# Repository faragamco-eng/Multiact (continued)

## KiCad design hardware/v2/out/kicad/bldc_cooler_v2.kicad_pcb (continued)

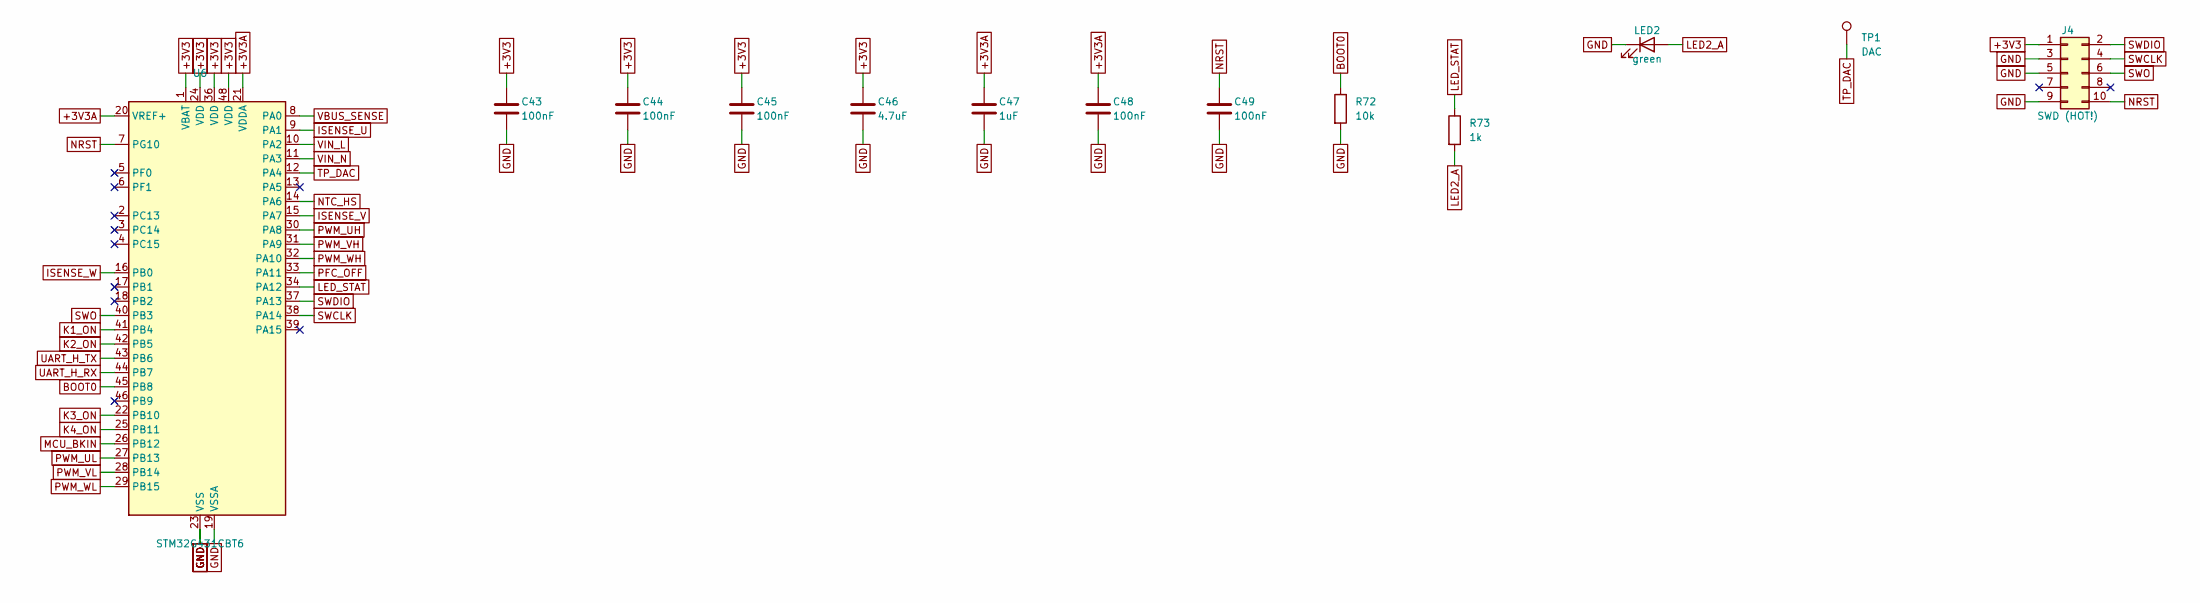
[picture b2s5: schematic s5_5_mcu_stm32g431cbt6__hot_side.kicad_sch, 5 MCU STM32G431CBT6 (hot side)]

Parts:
C43, C44, C45, C48, C49: 100nF; C_0603_1608Metric
C46: 4.7uF; C_0805_2012Metric
C47: 1uF; C_0603_1608Metric
J4: SWD (HOT!); PinHeader_2x05_P1.27mm_Vertical
LED2: green; LED_0805_2012Metric
R72: 10k; R_0603_1608Metric
R73: 1k; R_0603_1608Metric
TP1: DAC; TestPoint_Pad_D1.5mm
U6: STM32G431CBT6; LQFP-48_7x7mm_P0.5mm; MPN ST STM32G431CBT6

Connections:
+3V3: C43.1, C44.1, C45.1, C46.1, J4.1, U6.1 (VBAT), U6.24 (VDD), U6.36 (VDD), U6.48 (VDD); also elsewhere on the board
+3V3A: C47.1, C48.1, U6.20 (VREF+), U6.21 (VDDA); also elsewhere on the board
BOOT0: R72.1, U6.45 (PB8)
GND: C43.2, C44.2, C45.2, C46.2, C47.2, C48.2, C49.2, J4.3, J4.5, J4.9, LED2.1 (K), R72.2, U6.19 (VSSA), U6.23 (VSS), U6.35 (VSS), U6.47 (VSS); also elsewhere on the board
ISENSE_U: U6.9 (PA1); also elsewhere on the board
ISENSE_V: U6.15 (PA7); also elsewhere on the board
ISENSE_W: U6.16 (PB0); also elsewhere on the board
K1_ON: U6.41 (PB4); also elsewhere on the board
K2_ON: U6.42 (PB5); also elsewhere on the board
K3_ON: U6.22 (PB10); also elsewhere on the board
K4_ON: U6.25 (PB11); also elsewhere on the board
LED2_A: LED2.2 (A), R73.2
LED_STAT: R73.1, U6.34 (PA12)
MCU_BKIN: U6.26 (PB12); also elsewhere on the board
NRST: C49.1, J4.10, U6.7 (PG10)
NTC_HS: U6.14 (PA6); also elsewhere on the board
PFC_OFF: U6.33 (PA11); also elsewhere on the board
PWM_UH: U6.30 (PA8); also elsewhere on the board
PWM_UL: U6.27 (PB13); also elsewhere on the board
PWM_VH: U6.31 (PA9); also elsewhere on the board
PWM_VL: U6.28 (PB14); also elsewhere on the board
PWM_WH: U6.32 (PA10); also elsewhere on the board
PWM_WL: U6.29 (PB15); also elsewhere on the board
SWCLK: J4.4, U6.38 (PA14)
SWDIO: J4.2, U6.37 (PA13)
SWO: J4.6, U6.40 (PB3)
TP_DAC: TP1.1, U6.12 (PA4)
UART_H_RX: U6.44 (PB7); also elsewhere on the board
UART_H_TX: U6.43 (PB6); also elsewhere on the board
VBUS_SENSE: U6.8 (PA0); also elsewhere on the board
VIN_L: U6.10 (PA2); also elsewhere on the board
VIN_N: U6.11 (PA3); also elsewhere on the board

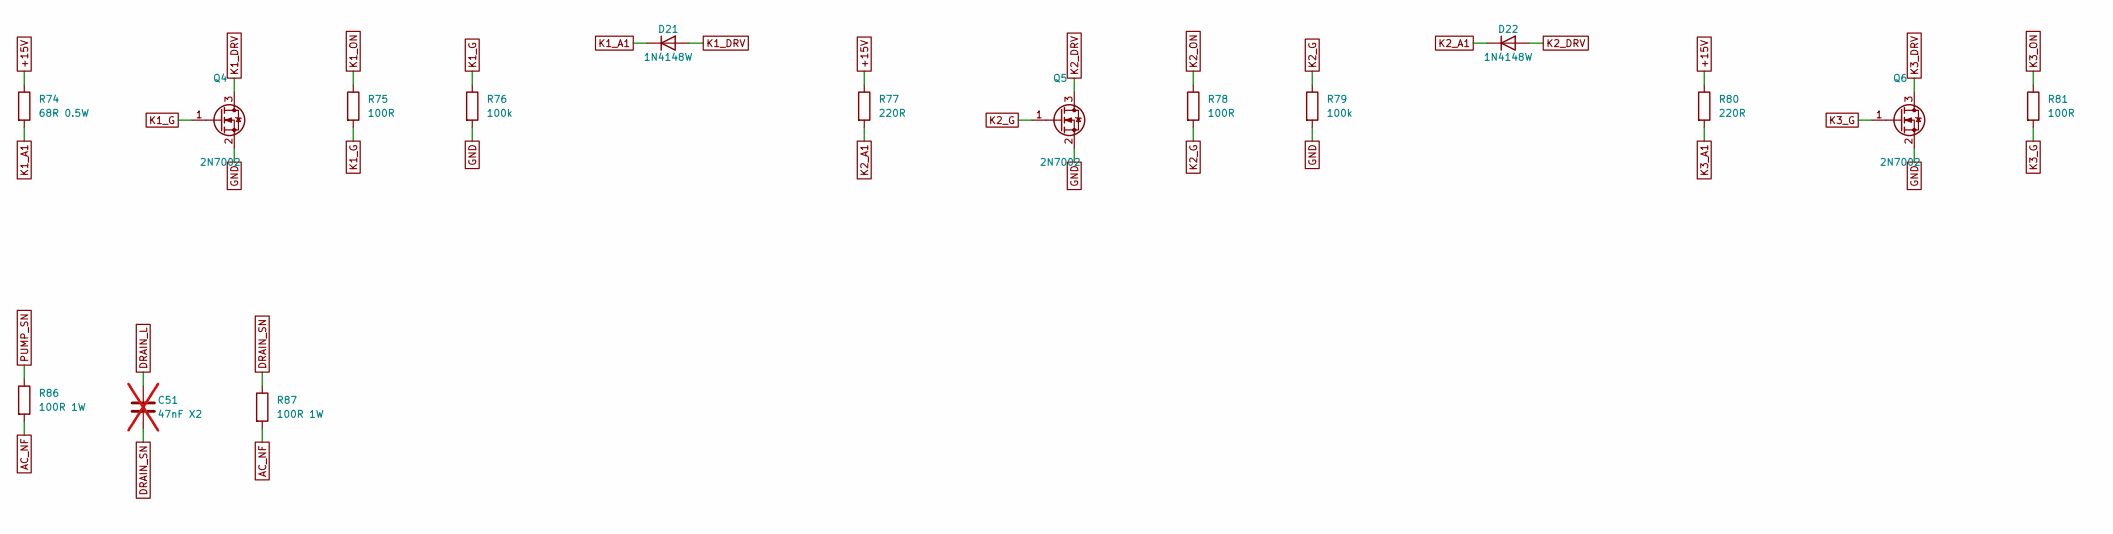
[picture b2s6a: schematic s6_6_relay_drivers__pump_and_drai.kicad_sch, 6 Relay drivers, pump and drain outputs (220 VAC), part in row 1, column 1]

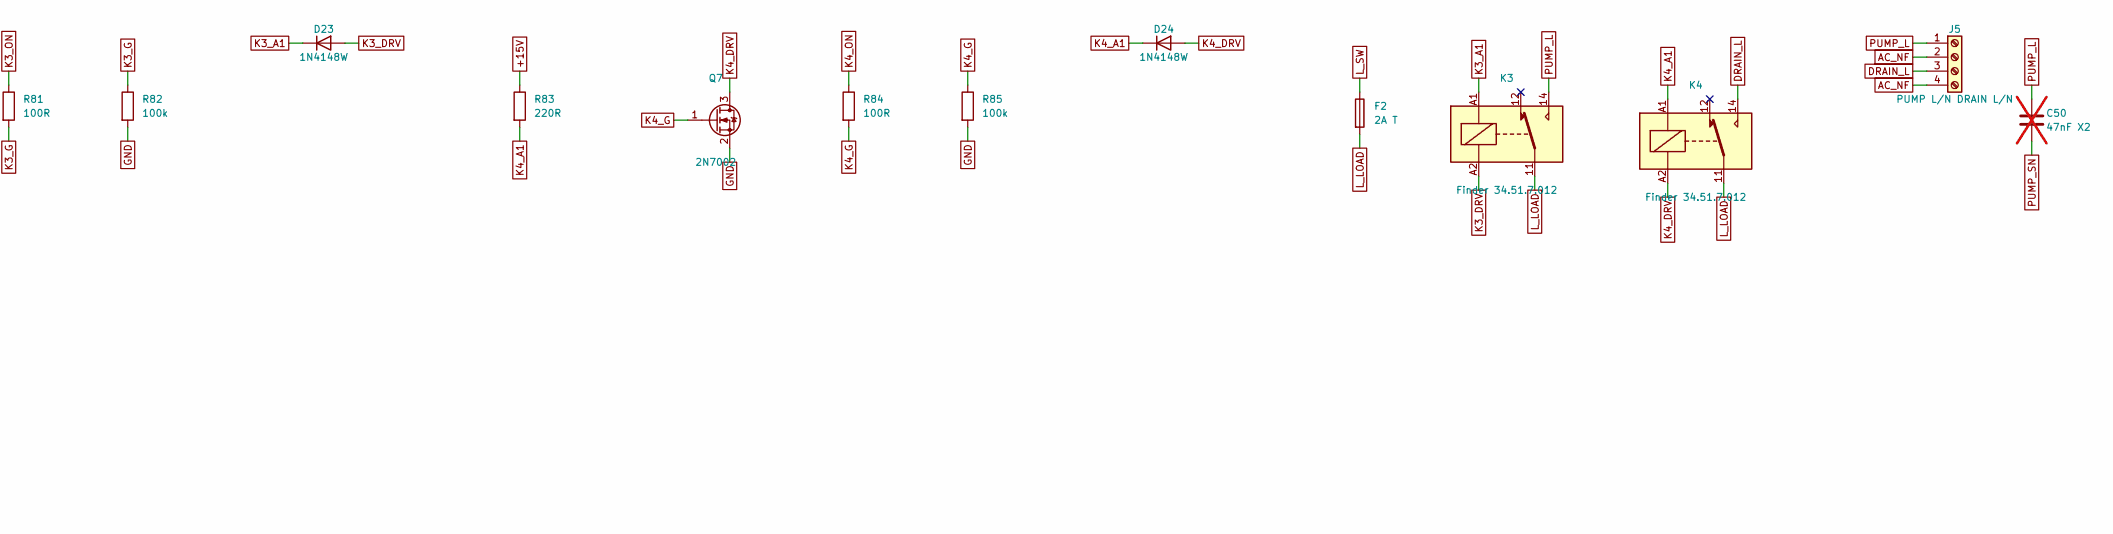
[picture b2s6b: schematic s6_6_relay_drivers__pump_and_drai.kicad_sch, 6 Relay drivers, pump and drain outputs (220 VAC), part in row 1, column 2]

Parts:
C50, C51: 47nF X2; C_Rect_L18.0mm_W6.0mm_P15.00mm_FKS3_FKP3; not fitted
D21, D22, D23, D24: 1N4148W; D_SOD-123; MPN 1N4148W
F2: 2A T; Fuseholder_Cylinder-5x20mm_Bulgin_FX0457_Horizontal_Closed; MPN 5x20 2 A time-lag
J5: PUMP L/N DRAIN L/N; TerminalBlock_Phoenix_MKDS-1,5-4-5.08_1x04_P5.08mm_Horizont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
K3, K4: Finder 34.51.7.012; Relay_SPDT_Finder_34.51_Vertical; MPN Finder 34.51.7.012.0010
Q4, Q5, Q6, Q7: 2N7002; SOT-23; MPN 2N7002
R74: 68R 0.5W; R_1206_3216Metric
R75, R78, R81, R84: 100R; R_0603_1608Metric
R76, R79, R82, R85: 100k; R_0603_1608Metric
R77, R80, R83: 220R; R_0603_1608Metric
R86, R87: 100R 1W; R_2512_6332Metric

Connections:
+15V: R74.1, R77.1, R80.1, R83.1; also elsewhere on the board
AC_NF: J5.2, J5.4, R86.2, R87.2; also elsewhere on the board
DRAIN_L: C51.1, J5.3, K4.14
DRAIN_SN: C51.2, R87.1
GND: Q4.2 (S), Q5.2 (S), Q6.2 (S), Q7.2 (S), R76.2, R79.2, R82.2, R85.2; also elsewhere on the board
K1_A1: D21.1 (K), R74.2; also elsewhere on the board
K1_DRV: D21.2 (A), Q4.3 (D); also elsewhere on the board
K1_G: Q4.1 (G), R75.2, R76.1
K1_ON: R75.1; also elsewhere on the board
K2_A1: D22.1 (K), R77.2; also elsewhere on the board
K2_DRV: D22.2 (A), Q5.3 (D); also elsewhere on the board
K2_G: Q5.1 (G), R78.2, R79.1
K2_ON: R78.1; also elsewhere on the board
K3_A1: D23.1 (K), K3.A1, R80.2
K3_DRV: D23.2 (A), K3.A2, Q6.3 (D)
K3_G: Q6.1 (G), R81.2, R82.1
K3_ON: R81.1; also elsewhere on the board
K4_A1: D24.1 (K), K4.A1, R83.2
K4_DRV: D24.2 (A), K4.A2, Q7.3 (D)
K4_G: Q7.1 (G), R84.2, R85.1
K4_ON: R84.1; also elsewhere on the board
L_LOAD: F2.2, K3.11, K4.11
L_SW: F2.1; also elsewhere on the board
PUMP_L: C50.1, J5.1, K3.14
PUMP_SN: C50.2, R86.1

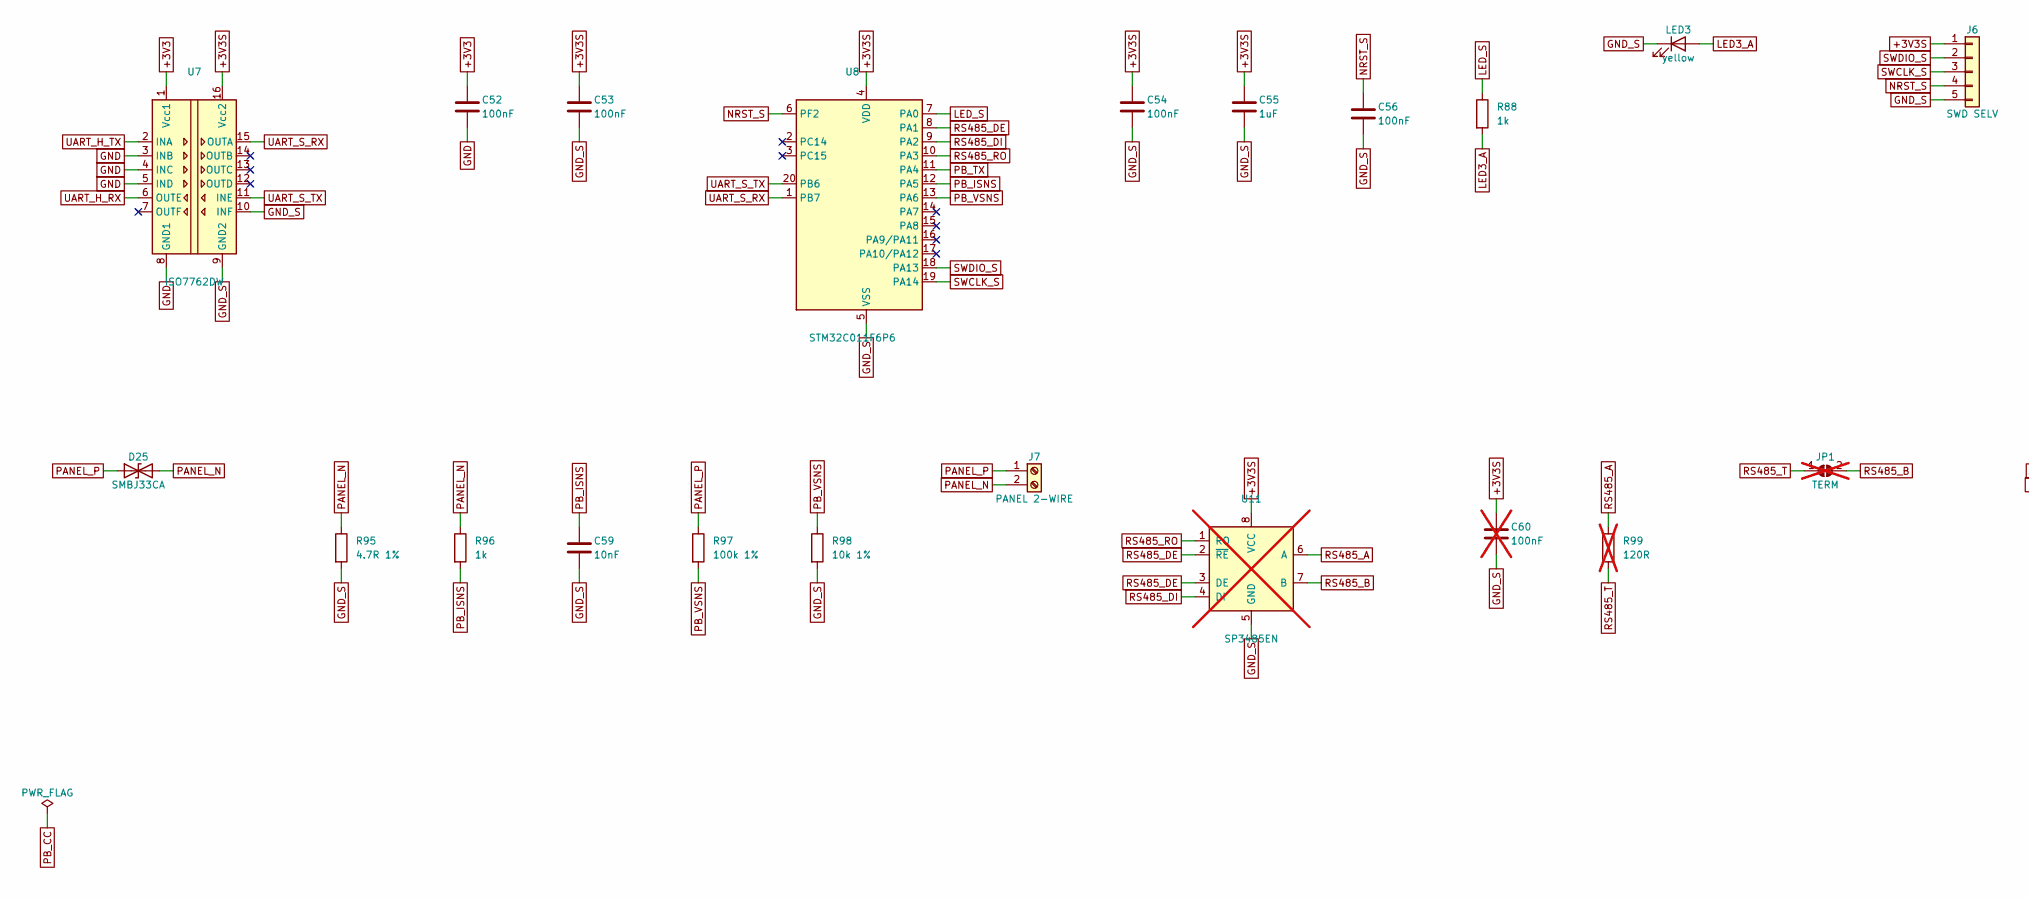
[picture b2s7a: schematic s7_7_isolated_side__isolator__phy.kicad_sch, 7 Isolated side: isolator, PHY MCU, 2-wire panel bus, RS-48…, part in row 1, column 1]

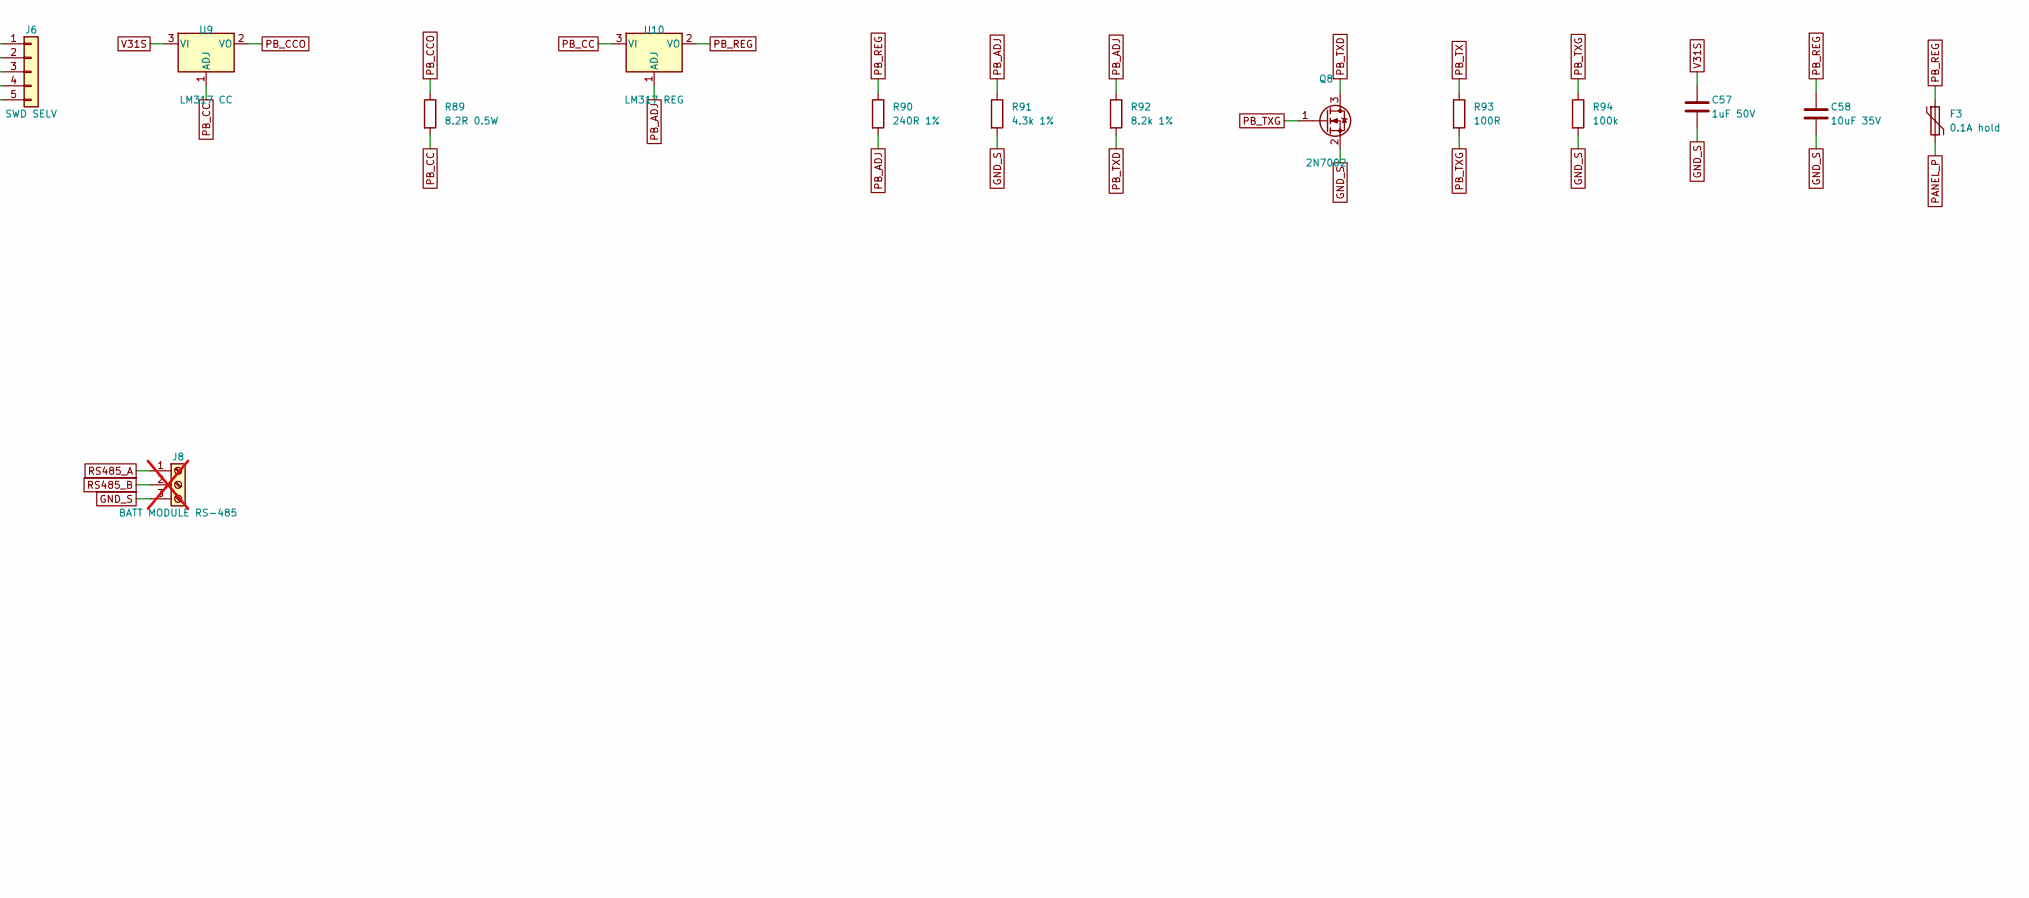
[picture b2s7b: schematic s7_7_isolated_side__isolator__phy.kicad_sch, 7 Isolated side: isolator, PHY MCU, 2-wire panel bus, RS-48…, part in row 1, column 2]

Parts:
C52, C53, C54, C56: 100nF; C_0603_1608Metric
C55: 1uF; C_0603_1608Metric
C57: 1uF 50V; C_1206_3216Metric
C58: 10uF 35V; C_1206_3216Metric
C59: 10nF; C_0603_1608Metric
C60: 100nF; C_0603_1608Metric; not fitted
D25: SMBJ33CA; D_SMB; MPN SMBJ33CA
F3: 0.1A hold; Fuse_1812_4532Metric; MPN Bourns MF-MSMF010
J6: SWD SELV; PinHeader_1x05_P2.54mm_Vertical
J7: PANEL 2-WIRE; TerminalBlock_Phoenix_MKDS-1,5-2-5.08_1x02_P5.08mm_Horizont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
J8: BATT MODULE RS-485; TerminalBlock_Phoenix_MKDS-1,5-3-5.08_1x03_P5.08mm_Horizont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; not fitted
JP1: TERM; SolderJumper-2_P1.3mm_Open_Pad1.0x1.5mm; not fitted
LED3: yellow; LED_0805_2012Metric
Q8: 2N7002; SOT-23; MPN 2N7002
R88, R96: 1k; R_0603_1608Metric
R89: 8.2R 0.5W; R_1206_3216Metric
R90: 240R 1%; R_0603_1608Metric
R91: 4.3k 1%; R_0603_1608Metric
R92: 8.2k 1%; R_0603_1608Metric
R93: 100R; R_0603_1608Metric
R94: 100k; R_0603_1608Metric
R95: 4.7R 1%; R_1206_3216Metric
R97: 100k 1%; R_0603_1608Metric
R98: 10k 1%; R_0603_1608Metric
R99: 120R; R_0603_1608Metric; not fitted
U7: ISO7762DW; SOIC-16W_7.5x10.3mm_P1.27mm; MPN TI ISO7762DWR (reinforced 5 kVrms, SOIC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
U8: STM32C011F6P6; TSSOP-20_4.4x6.5mm_P0.65mm; MPN ST STM32C011F6P6
U9: LM317 CC; TO-220-3_Vertical; MPN LM317T (small heatsink)
U10: LM317 REG; TO-220-3_Vertical; MPN LM317T
U11: SP3485EN; SOIC-8_3.9x4.9mm_P1.27mm; MPN MaxLinear SP3485EN (3.3 V half duplex); not fitted

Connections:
+3V3: C52.1, U7.1 (Vcc1); also elsewhere on the board
+3V3S: C53.1, C54.1, C55.1, C60.1, J6.1, U7.16 (Vcc2), U8.4 (VDD), U11.8 (VCC); also elsewhere on the board
GND: C52.2, U7.3 (INB), U7.4 (INC), U7.5 (IND), U7.8 (GND1); also elsewhere on the board
GND_S: C53.2, C54.2, C55.2, C56.2, C57.2, C58.2, C59.2, C60.2, J6.5, J8.3, LED3.1 (K), Q8.2 (S), R91.2, R94.2, R95.2, R98.2, U7.9 (GND2), U7.10 (INF), U8.5 (VSS), U11.5 (GND); also elsewhere on the board
LED3_A: LED3.2 (A), R88.2
LED_S: R88.1, U8.7 (PA0)
NRST_S: C56.1, J6.4, U8.6 (PF2)
PANEL_N: D25.2 (A2), J7.2, R95.1, R96.1
PANEL_P: D25.1 (A1), F3.2, J7.1, R97.1; also elsewhere on the board
PB_ADJ: R90.2, R91.1, R92.1, U10.1 (ADJ)
PB_CC: R89.2, U9.1 (ADJ), U10.3 (VI)
PB_CCO: R89.1, U9.2 (VO)
PB_ISNS: C59.1, R96.2, U8.12 (PA5)
PB_REG: C58.1, F3.1, R90.1, U10.2 (VO)
PB_TX: R93.1, U8.11 (PA4)
PB_TXD: Q8.3 (D), R92.2
PB_TXG: Q8.1 (G), R93.2, R94.1
PB_VSNS: R97.2, R98.1, U8.13 (PA6)
RS485_A: J8.1, R99.1, U11.6 (A)
RS485_B: J8.2, JP1.2 (B), U11.7 (B)
RS485_DE: U8.8 (PA1), U11.2 (~RE), U11.3 (DE)
RS485_DI: U8.9 (PA2), U11.4 (DI)
RS485_RO: U8.10 (PA3), U11.1 (RO)
RS485_T: JP1.1 (A), R99.2
SWCLK_S: J6.3, U8.19 (PA14)
SWDIO_S: J6.2, U8.18 (PA13)
UART_H_RX: U7.6 (OUTE); also elsewhere on the board
UART_H_TX: U7.2 (INA); also elsewhere on the board
UART_S_RX: U7.15 (OUTA), U8.1 (PB7)
UART_S_TX: U7.11 (INE), U8.20 (PB6)
V31S: C57.1, U9.3 (VI); also elsewhere on the board

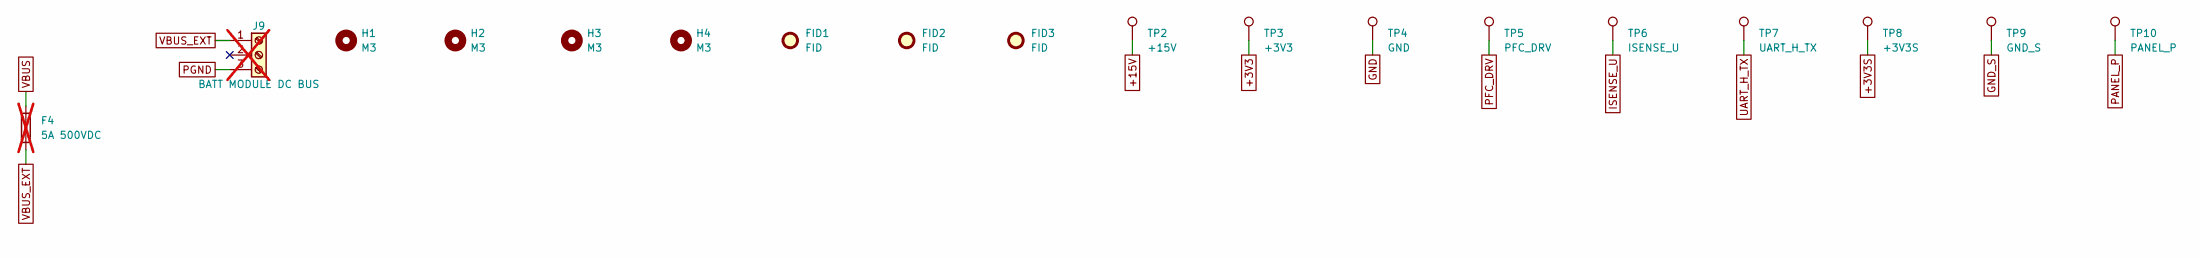
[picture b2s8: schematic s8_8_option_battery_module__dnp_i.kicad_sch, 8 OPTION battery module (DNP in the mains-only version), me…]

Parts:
F4: 5A 500VDC; Fuseholder_Cylinder-5x20mm_Bulgin_FX0457_Horizontal_Closed; MPN 5x20 ceramic, DC rated >= 500 V (e.g. L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; not fitted
FID1, FID2, FID3: FID; Fiducial_1mm_Mask2mm
H1, H2, H3, H4: M3; MountingHole_3.2mm_M3
J9: BATT MODULE DC BUS; TerminalBlock_Phoenix_MKDS-1,5-3-5.08_1x03_P5.08mm_Horizont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; not fitted
TP2: +15V; TestPoint_Pad_D1.5mm
TP3: +3V3; TestPoint_Pad_D1.5mm
TP4: GND; TestPoint_Pad_D1.5mm
TP5: PFC_DRV; TestPoint_Pad_D1.5mm
TP6: ISENSE_U; TestPoint_Pad_D1.5mm
TP7: UART_H_TX; TestPoint_Pad_D1.5mm
TP8: +3V3S; TestPoint_Pad_D1.5mm
TP9: GND_S; TestPoint_Pad_D1.5mm
TP10: PANEL_P; TestPoint_Pad_D1.5mm

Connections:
+3V3: TP3.1; also elsewhere on the board
+3V3S: TP8.1; also elsewhere on the board
+15V: TP2.1; also elsewhere on the board
GND: TP4.1; also elsewhere on the board
GND_S: TP9.1; also elsewhere on the board
ISENSE_U: TP6.1; also elsewhere on the board
PANEL_P: TP10.1; also elsewhere on the board
PFC_DRV: TP5.1; also elsewhere on the board
PGND: J9.3; also elsewhere on the board
UART_H_TX: TP7.1; also elsewhere on the board
VBUS: F4.1; also elsewhere on the board
VBUS_EXT: F4.2, J9.1

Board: 2 copper layers, 289 parts (0 on the bottom side), 172 nets, no tracks yet.

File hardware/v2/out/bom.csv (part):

Qty,References,Value,MPN / description,Footprint,Populate
1,J1,AC IN L/N/PE,"Phoenix MKDS 1,5/3-5,08","TerminalBlock_Phoenix:TerminalBlock_Phoenix_MKDS-1,5-3-5.08_1x03_P5.08mm_Horizontal",yes
1,F1,10A T 250VAC,5x20 ceramic 10 A time-lag,Fuse:Fuseholder_Cylinder-5x20mm_Bulgin_FX0457_Horizontal_Closed,yes
1,RV1,S14K385,EPCOS S14K385,Varistor:RV_Disc_D15.5mm_W11mm_P7.5mm,yes
2,RV2 RV3,S14K385,,Varistor:RV_Disc_D15.5mm_W11mm_P7.5mm,yes
1,GDT1,GDT 600V,axial 2-electrode GDT 600 V (e.g. Bourns 2026-60 / EPCOS EC600X),Custom:GDT_Axial_P15.24mm,yes
1,CX1,470nF X2,X2 310VAC,Capacitor_THT:C_Rect_L18.0mm_W7.0mm_P15.00mm_FKS3_FKP3,yes
2,R1 R2,470k,,Resistor_SMD:R_1206_3216Metric,yes
1,L1,2x4.7mH 10A,"toroidal CM choke 2 x 4.7 mH, >= 10 A (e.g. Schaffner RN series); verify pin map",Custom:CMC_Toroid_4P_25x15mm,yes
1,CX2,470nF X2,,Capacitor_THT:C_Rect_L18.0mm_W7.0mm_P15.00mm_FKS3_FKP3,yes
2,CY1 CY2,2.2nF Y2,Y2 300VAC,Capacitor_THT:C_Disc_D11.0mm_W5.0mm_P7.50mm,yes
1,K1,Finder 40.11.9.012,"Finder 40.11.9.012.0000 (10 A, 12 V coil)",Relay_THT:Relay_SPDT_Finder_40.11,yes
3,K2 K3 K4,Finder 34.51.7.012,Finder 34.51.7.012.0010,Relay_THT:Relay_SPDT_Finder_34.51_Vertical,yes
1,PTC1,PTC 120R inrush,"inrush PTC rated >= 80 J at 265 VAC (940 uF @ 373 V = 65 J), e.g. TDK/EPCOS J1xx series - verify",Capacitor_THT:C_Disc_D11.0mm_W5.0mm_P7.50mm,yes
3,D1 D2 D3,1N4007,1N4007,Diode_THT:D_DO-41_SOD81_P10.16mm_Horizontal,yes
4,C1 C35 C40 C36,100nF 630V,,Capacitor_THT:C_Rect_L18.0mm_W6.0mm_P15.00mm_FKS3_FKP3,yes
1,D29,UF4007,UF4007 (1000 V),Diode_THT:D_DO-41_SOD81_P10.16mm_Horizontal,yes
14,R3 R4 R5 R7 R8 R9 R22 R23 R24 R25 R32 R33 R34 R35,1M,,Resistor_SMD:R_1206_3216Metric,yes
5,R6 R10 R60 R61 R62,10k 0.1%,,Resistor_SMD:R_0603_1608Metric,yes
2,D4 D5,BAT54S,BAT54S,Package_TO_SOT_SMD:SOT-23,yes
5,C2 C3 C7 C8 C41,1nF,,Capacitor_SMD:C_0603_1608Metric,yes
7,R11 R12 R53 R70 R73 R88 R96,1k,,Resistor_SMD:R_0603_1608Metric,yes
1,BR1,GBU1010,GBU1010 (10 A 1000 V) on heatsink,Diode_THT:Diode_Bridge_Vishay_GBU,yes
2,C4 C34,1uF 630V,,Capacitor_THT:C_Rect_L26.5mm_W8.5mm_P22.50mm_MKS4,yes
1,L2,470uH 13A,"toroid ~46 mm OD (e.g. Kool Mu 0077083A7 or High Flux 58083), 470 uH at 11 A, Isat >= 13 A",Inductor_THT:L_Toroid_Vertical_L46.0mm_W19.1mm_P21.80mm_Bourns_5700,yes
1,D6,SiC 650V 8A,Wolfspeed C3D08065A / Infineon IDH08G65C6,Package_TO_SOT_THT:TO-220-2_Vertical,yes
1,D7,P600M,P600M / 1N5408 inrush bypass,Diode_THT:D_DO-201AD_P15.24mm_Horizontal,yes
1,Q1,650V 95mOhm SJ,"Infineon IPW65R095C7 / ST STW40N60M6 (heatsink, insulated)",Package_TO_SOT_THT:TO-247-3_Vertical,yes
2,R13 R17,10R,,Resistor_SMD:R_0603_1608Metric,yes
15,R14 R108 R110 R112 R114 R116 R118 R41 R43 R45 R47 R49 R51 R52 R72,10k,,Resistor_SMD:R_0603_1608Metric,yes
1,D8,BZT52C18,BZT52C18,Diode_SMD:D_SOD-123,yes
2,R15 R16,50m 3W,,Resistor_SMD:R_2512_6332Metric,yes
1,U1,NCP1653,onsemi NCP1653ADR2G (67 kHz),Package_SO:SOIC-8_3.9x4.9mm_P1.27mm,yes
1,C5,22uF 25V,,Capacitor_THT:CP_Radial_D8.0mm_P3.50mm,yes
20,C6 C17 C20 C29 C64 C31 C66 C33 C68 C27 C42 C43 C44 C45 C48 C49 C52 C53 C54 C56,100nF,,Capacitor_SMD:C_0603_1608Metric,yes
4,R18 R19 R20 R21,470k 1%,,Resistor_SMD:R_1206_3216Metric,yes
1,R26,4.7k,,Resistor_SMD:R_0603_1608Metric,yes
1,C9,100pF,,Capacitor_SMD:C_0603_1608Metric,yes
1,R27,22k,,Resistor_SMD:R_0603_1608Metric,yes
1,C10,220pF,,Capacitor_SMD:C_0603_1608Metric,yes
1,C11,1uF,,Capacitor_SMD:C_0805_2012Metric,yes
6,Q2 Q4 Q5 Q6 Q7 Q8,2N7002,2N7002,Package_TO_SOT_SMD:SOT-23,yes
6,R28 R76 R79 R82 R85 R94,100k,,Resistor_SMD:R_0603_1608Metric,yes
2,C12 C13,470uF 450V,"470 uF 450 V 105 C >= 5000 h snap-in D35 (e.g. Nichicon LGN/LGU, TDK B43544, Rubycon USR)",Capacitor_THT:CP_Radial_D35.0mm_P10.00mm_SnapIn,yes
3,R29 R30 R31,100k,,Resistor_SMD:R_1206_3216Metric,yes
1,LED1,red HV,"high-efficiency red, 'HIGH VOLTAGE'",LED_SMD:LED_0805_2012Metric,yes
1,Q3,1500V 4A,"ST STW4N150 (on main heatsink, insulated)",Package_TO_SOT_THT:TO-247-3_Vertical,yes
4,D9 D10 D11 D12,1N4764A 100V,1N4764A,Diode_THT:D_DO-41_SOD81_P10.16mm_Horizontal,yes
1,D13,BZT52C15,BZT52C15,Diode_SMD:D_SOD-123,yes
1,C14,10uF 450V,,Capacitor_THT:CP_Radial_D10.0mm_P5.00mm,yes
1,T1,EF20 flyback,"custom, see calc/transformer spec",Transformer_THT:Transformer_Myrra_EF20_7408x,yes
1,U2,VIPer26LN,ST VIPer26LN (60 kHz),Package_DIP:DIP-8-N6_W7.62mm,yes
1,D14,UF4007,UF4007,Diode_THT:D_DO-41_SOD81_P10.16mm_Horizontal,yes
1,D15,P6KE200CA,"P6KE200CA (bidirectional, 200 V clamp)",Diode_THT:D_DO-41_SOD81_P10.16mm_Horizontal,yes
2,D16 D20,ES1D,ES1D,Diode_SMD:D_SMA,yes
1,C15,220uF 35V,,Capacitor_THT:CP_Radial_D8.0mm_P3.50mm,yes
5,D17 D21 D22 D23 D24,1N4148W,1N4148W,Diode_SMD:D_SOD-123,yes
1,C16,10uF 35V,,Capacitor_THT:CP_Radial_D8.0mm_P3.50mm,yes
1,R36,36k 1%,,Resistor_SMD:R_0603_1608Metric,yes
3,R37 R71 R98,10k 1%,,Resistor_SMD:R_0603_1608Metric,yes
1,R38,2.2k,,Resistor_SMD:R_0603_1608Metric,yes
1,C18,2.2nF,,Capacitor_SMD:C_0603_1608Metric,yes
1,R39,DNP,,Resistor_SMD:R_0603_1608Metric,yes
1,D18,SMBJ18CA,SMBJ18CA,Diode_SMD:D_SMB,yes
1,U3,AP63203WU,Diodes AP63203WU (fixed 3.3 V),Package_TO_SOT_SMD:TSOT-23-6,yes
5,C19 C63 C65 C67 C26,10uF 25V,,Capacitor_SMD:C_1206_3216Metric,yes
1,L3,6.8uH 1A,Bourns SRN6045TA-6R8M,Inductor_SMD:L_Bourns_SRN6045TA,yes
1,C21,22uF 10V,,Capacitor_SMD:C_1206_3216Metric,yes
1,FB1,600R@100MHz,ferrite bead,Inductor_SMD:L_0603_1608Metric,yes
4,C22 C24 C47 C55,1uF,,Capacitor_SMD:C_0603_1608Metric,yes
1,D19,SS34,SS34,Diode_SMD:D_SMA,yes
1,C23,220uF 16V,,Capacitor_THT:CP_Radial_D8.0mm_P3.50mm,yes
1,U4,AP2112K-3.3,Diodes AP2112K-3.3TRG1,Package_TO_SOT_SMD:SOT-23-5,yes
1,C25,470uF 50V,,Capacitor_THT:CP_Radial_D10.0mm_P5.00mm,yes
3,U5 U12 U13,IRS2186PBF,Infineon IRS2186PBF (DIP-8 in socket),Package_DIP:DIP-8_W7.62mm_Socket,yes
6,Q9 Q10 Q11 Q12 Q13 Q14,600V 18A,ST STW24N60DM2 (fast body diode) / alt. STGW20H60DF IGBT,Package_TO_SOT_THT:TO-247-3_Vertical,yes
9,R107 R109 R119 R111 R113 R120 R115 R117 R121,10R,,Resistor_SMD:R_1206_3216Metric,yes
3,D26 D27 D28,UF4007,"UF4007 (1000 V, 75 ns)",Diode_THT:D_DO-41_SOD81_P10.16mm_Horizontal,yes
3,C28 C30 C32,4.7uF 25V X7R,,Capacitor_SMD:C_1206_3216Metric,yes
11,R40 R42 R44 R46 R48 R50 R75 R78 R81 R84 R93,100R,,Resistor_SMD:R_0603_1608Metric,yes
2,C69 C59,10nF,,Capacitor_SMD:C_0603_1608Metric,yes
1,J10,TSW 90C NC,"KSD301 90 C normally closed, on heatsink",Connector_PinHeader_2.54mm:PinHeader_1x02_P2.54mm_Vertical,yes
3,R54 R55 R56,25m 2W,,Resistor_SMD:R_2512_6332Metric,yes
3,R57 R58 R59,1k 0.1%,,Resistor_SMD:R_0603_1608Metric,yes
3,C37 C38 C39,470pF C0G,,Capacitor_SMD:C_0603_1608Metric,yes
1,NT1,STAR,,NetTie:NetTie-2_SMD_Pad0.5mm,yes
1,J2,MOTOR U/V/W/PE,,"TerminalBlock_Phoenix:TerminalBlock_Phoenix_MKDS-1,5-4-5.08_1x04_P5.08mm_Horizontal",yes
3,R66 R67 R68,330k 1%,,Resistor_SMD:R_1206_3216Metric,yes
1,R69,6.65k 0.1%,,Resistor_SMD:R_0603_1608Metric,yes
1,J3,NTC 10k B3435,screw-lug NTC 10k B3435 on heatsink,Connector_PinHeader_2.54mm:PinHeader_1x02_P2.54mm_Vertical,yes
1,U6,STM32G431CBT6,ST STM32G431CBT6,Package_QFP:LQFP-48_7x7mm_P0.5mm,yes
1,C46,4.7uF,,Capacitor_SMD:C_0805_2012Metric,yes
1,LED2,green,,LED_SMD:LED_0805_2012Metric,yes
1,TP1,DAC,,TestPoint:TestPoint_Pad_D1.5mm,yes
1,J4,SWD (HOT!),,Connector_PinHeader_1.27mm:PinHeader_2x05_P1.27mm_Vertical,yes
1,R74,68R 0.5W,,Resistor_SMD:R_1206_3216Metric,yes
3,R77 R80 R83,220R,,Resistor_SMD:R_0603_1608Metric,yes
1,F2,2A T,5x20 2 A time-lag,Fuse:Fuseholder_Cylinder-5x20mm_Bulgin_FX0457_Horizontal_Closed,yes
1,J5,PUMP L/N DRAIN L/N,,"TerminalBlock_Phoenix:TerminalBlock_Phoenix_MKDS-1,5-4-5.08_1x04_P5.08mm_Horizontal",yes
2,C50 C51,47nF X2,,Capacitor_THT:C_Rect_L18.0mm_W6.0mm_P15.00mm_FKS3_FKP3,OPTION/DNP
2,R86 R87,100R 1W,,Resistor_SMD:R_2512_6332Metric,yes
1,U7,ISO7762DW,"TI ISO7762DWR (reinforced 5 kVrms, SOIC-16 wide)",Package_SO:SOIC-16W_7.5x10.3mm_P1.27mm,yes
1,U8,STM32C011F6P6,ST STM32C011F6P6,Package_SO:TSSOP-20_4.4x6.5mm_P0.65mm,yes
1,LED3,yellow,,LED_SMD:LED_0805_2012Metric,yes
1,J6,SWD SELV,,Connector_PinHeader_2.54mm:PinHeader_1x05_P2.54mm_Vertical,yes
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
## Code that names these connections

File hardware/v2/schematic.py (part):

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  {1: "AC_LF0", 2: "AC_N"}, mpn="EPCOS S14K385", note="385 VAC: survives 380-440 V neutral loss")
P("RV2", "Device:Varistor", "S14K385", "Varistor:RV_Disc_D15.5mm_W11mm_P7.5mm", {1: "AC_LF0", 2: "SURGE_PE"})
P("RV3", "Device:Varistor", "S14K385", "Varistor:RV_Disc_D15.5mm_W11mm_P7.5mm", {1: "AC_N", 2: "SURGE_PE"})
P("GDT1", "Device:GDT_2Pin", "GDT 600V", "Custom:GDT_Axial_P15.24mm", {1: "SURGE_PE", 3: "PE"},
  mpn="axial 2-electrode GDT 600 V (e.g. Bourns 2026-60 / EPCOS EC600X)")
P("CX1", "Device:C", "470nF X2", "Capacitor_THT:C_Rect_L18.0mm_W7.0mm_P15.00mm_FKS3_FKP3",
  {1: "AC_LF0", 2: "AC_N"}, mpn="X2 310VAC")
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R("R2", "470k", "XDIS", "AC_N", R1206, "X-cap discharge")
P("L1", "Device:Filter_EMI_CommonMode", "2x4.7mH 10A",
  "Custom:CMC_Toroid_4P_25x15mm",
  {1: "AC_LF0", 2: "AC_LF", 3: "AC_N", 4: "AC_NF"}, mpn="toroidal CM choke 2 x 4.7 mH, >= 10 A (e.g. Schaffner RN series); verify pin map")
P("CX2", "Device:C", "470nF X2", "Capacitor_THT:C_Rect_L18.0mm_W7.0mm_P15.00mm_FKS3_FKP3", {1: "AC_LF", 2: "AC_NF"})
P("CY1", "Device:C", "2.2nF Y2", "Capacitor_THT:C_Disc_D11.0mm_W5.0mm_P7.50mm", {1: "AC_LF", 2: "PE"}, mpn="Y2 300VAC")
P("CY2", "Device:C", "2.2nF Y2", "Capacitor_THT:C_Disc_D11.0mm_W5.0mm_P7.50mm", {1: "AC_NF", 2: "PE"}, mpn="Y2 300VAC")
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# ========================================================================
MCU = {
    1: ("VBAT", "+3V3"), 2: ("PC13", "NC_PC13"), 3: ("PC14", "NC_PC14"), 4: ("PC15", "NC_PC15"),
    5: ("PF0", "NC_PF0"), 6: ("PF1", "NC_PF1"), 7: ("PG10", "NRST"),
    8: ("PA0", "VBUS_SENSE"), 9: ("PA1", "ISENSE_U"), 10: ("PA2", "VIN_L"), 11: ("PA3", "VIN_N"),
    12: ("PA4", "TP_DAC"), 13: ("PA5", "NC_PA5"), 14: ("PA6", "NTC_HS"), 15: ("PA7", "ISENSE_V"),
    16: ("PB0", "ISENSE_W"), 17: ("PB1", "NC_PB1"), 18: ("PB2", "NC_PB2"), 19: ("VSSA", "GND"),
    20: ("VREF+", "+3V3A"), 21: ("VDDA", "+3V3A"), 22: ("PB10", "K3_ON"), 23: ("VSS", "GND"), 24: ("VDD", "+3V3"),
    25: ("PB11", "K4_ON"), 26: ("PB12", "MCU_BKIN"), 27: ("PB13", "PWM_UL"), 28: ("PB14", "PWM_VL"),
    29: ("PB15", "PWM_WL"), 30: ("PA8", "PWM_UH"), 31: ("PA9", "PWM_VH"), 32: ("PA10", "PWM_WH"),
    33: ("PA11", "PFC_OFF"), 34: ("PA12", "LED_STAT"), 35: ("VSS", "GND"), 36: ("VDD", "+3V3"),
    37: ("PA13", "SWDIO"), 38: ("PA14", "SWCLK"), 39: ("PA15", "NC_PA15"), 40: ("PB3", "SWO"),
    41: ("PB4", "K1_ON"), 42: ("PB5", "K2_ON"), 43: ("PB6", "UART_H_TX"), 44: ("PB7", "UART_H_RX"),
    45: ("PB8", "BOOT0"), 46: ("PB9", "NC_PB9"), 47: ("VSS", "GND"), 48: ("VDD", "+3V3"),
}
P("U6", "MCU_ST_STM32G4:STM32G431CBTx", "STM32G431CBT6", "Package_QFP:LQFP-48_7x7mm_P0.5mm",
  {k: v[1] for k, v in MCU.items()}, names={k: v[0] for k, v in MCU.items()}, mpn="ST STM32G431CBT6")
# required alternate functions (validated against ST open pin data)
MCU_FUNCS = {
    "PA0": "ADC1_IN1", "PA1": "OPAMP1_VINP", "PA2": "ADC1_IN3", "PA3": "ADC1_IN4", "PA6": "ADC2_IN3",
    "PA7": "OPAMP2_VINP", "PB0": "OPAMP3_VINP", "PA4": "DAC1_OUT1",
    "PA8": "TIM1_CH1", "PA9": "TIM1_CH2", "PA10": "TIM1_CH3", "PB13": "TIM1_CH1N", "PB14": "TIM1_CH2N",
    "PB15": "TIM1_CH3N", "PB12": "TIM1_BKIN", "PB6": "USART1_TX", "PB7": "USART1_RX",
    "PA13": "SYS_JTMS-SWDIO", "PA14": "SYS_JTCK-SWCLK", "PB3": "SYS_JTDO-SWO",
}
MCU_FUNCS_EXTRA = {"PA1": "COMP1_INP", "PA7": "COMP2_INP", "PB0": "COMP4_INP"}   # per-phase over-current
for k in (24, 36, 48):
    C(f"C{43+(k-24)//12}", "100nF", "+3V3", "GND")
C("C46", "4.7uF", "+3V3", "GND", C0805)
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  note="ch A hot->SELV, ch E SELV->hot; unused inputs grounded; slot under the package, 8 mm creepage")
C("C52", "100nF", "+3V3", "GND")
C("C53", "100nF", "+3V3S", "GND_S")
PHY = {1: ("PB7", "UART_S_RX"), 2: ("PC14", "NC_S14"), 3: ("PC15", "NC_S15"), 4: ("VDD", "+3V3S"), 5: ("VSS", "GND_S"),
       6: ("PF2", "NRST_S"), 7: ("PA0", "LED_S"), 8: ("PA1", "RS485_DE"), 9: ("PA2", "RS485_DI"), 10: ("PA3", "RS485_RO"),
       11: ("PA4", "PB_TX"), 12: ("PA5", "PB_ISNS"), 13: ("PA6", "PB_VSNS"), 14: ("PA7", "NC_S7"), 15: ("PA8", "NC_S8"),
       16: ("PA9", "NC_S16"), 17: ("PA10", "NC_S17"), 18: ("PA13", "SWDIO_S"), 19: ("PA14", "SWCLK_S"), 20: ("PB6", "UART_S_TX")}
P("U8", "MCU_ST_STM32C0:STM32C011F6Px", "STM32C011F6P6", "Package_SO:TSSOP-20_4.4x6.5mm_P0.65mm",
  {k: v[1] for k, v in PHY.items()}, names={1: "PB7", 4: "VDD", 5: "VSS", 6: "PF2", 7: "PA0", 8: "PA1", 9: "PA2",
                                             10: "PA3", 11: "PA4", 12: "PA5", 13: "PA6", 18: "PA13", 19: "PA14", 20: "PB6"},
  mpn="ST STM32C011F6P6")
PHY_FUNCS = {"PB7": "USART1_RX", "PB6": "USART1_TX", "PA2": "USART2_TX", "PA3": "USART2_RX", "PA1": "USART2_DE",
             "PA5": "ADC1_IN5", "PA6": "ADC1_IN6"}
C("C54", "100nF", "+3V3S", "GND_S")
C("C55", "1uF", "+3V3S", "GND_S")
C("C56", "100nF", "NRST_S", "GND_S")
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
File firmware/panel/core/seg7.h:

/*
 * seg7.h - Text for the 4-digit 7-segment display of the basic panel
 * (hardware/panel: DS1 CC56-12, segments a..g,dp on IO1/IO2/IO42..IO37, digits on Q2..Q5).
 *
 *   "CO 7"  cool, speed 7      "FA10"  fan only, speed 10     "PU  "  pump only
 *   "Pr 2"  pre-wet, 2 min     "dr 4"  dry-out, 4 min         "E- 4"  alarm E4
 *   "----"  no drive           "UP45"  drive update 45 %      "    "  off
 */
#ifndef SEG7_H
#define SEG7_H
#include <stdint.h>
#include "panel.h"

#define SEG_A 0x01u
#define SEG_B 0x02u
#define SEG_C 0x04u
#define SEG_D 0x08u
#define SEG_E 0x10u
#define SEG_F 0x20u
#define SEG_G 0x40u
#define SEG_DP 0x80u

uint8_t seg7_char(char c);                                 /* segment bits of one character */
void    seg7_text(const ui_view_t *v, char out[5]);        /* 4 characters + NUL           */
/* LED bits for the 5th multiplex phase: a POWER, b PUMP, c FAN, d TIMER, e ALARM, f WIFI */
uint8_t seg7_leds(const ui_view_t *v);
#endif
